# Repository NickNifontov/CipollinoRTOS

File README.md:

CipollinoRTOS 

Sin wave invertor (HRPWM, 35kHz). Replacement for TL/EG PWM .

@Copyright (c) Nick Nifontov. All rights reserved.

E-mail: 3318798@gmail.com

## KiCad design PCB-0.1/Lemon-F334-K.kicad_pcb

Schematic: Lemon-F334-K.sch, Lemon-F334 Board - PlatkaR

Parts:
BZ1: Buzzer; Buzzer_TDK_PS1240P02BT_D12.2mm_H6.5mm
BZ2: Buzzer; MagneticBuzzer_Kingstate_KCG0601
BZ3: Buzzer; Buzzer_12x9.5RM7.6
C1, C3, C5, C7, C8, C14, C15, C23, C24, C27, C31, C36, C37, C38, C39, C40: 100nf; C_0805_2012Metric; LCSC Part #（optional） C49678
C2, C4, C6, C16, C17, C18, C19, C25, C26, C28, C29, C43, C44, C45, C47, C51: 10uf; C_0805_2012Metric; LCSC Part #（optional） C15850
C9, C10: 12pf; C_0805_2012Metric; LCSC Part #（optional） C1792
C11, C12, C13, C20, C21, C22, C46, C48, C49, C50: 10uf; C_1206_3216Metric; LCSC Part #（optional） C13585
C30: 220nf; C_0805_2012Metric; LCSC Part #（optional） C5378
C32, C34: 100pf; C_0805_2012Metric; LCSC Part #（optional） C1790
C33, C35: 1nf; C_0805_2012Metric; LCSC Part #（optional） C46653
C41, C42: 100uf; CP_EIA-3528-21_Kemet-B
D1: S210; D_SMA; LCSC Part #（optional） C14996
D2, D3, D4, D5, D6, D8, D9, D11, D12, D13, D14, D15, D24, D25: D_Zener_Small_ALT; D_MiniMELF; LCSC Part #（optional） C8056
D7, D10, D26, D27: BAS; D_SOD-123; LCSC Part #（optional） C8598
D16, D18, D20, D22: LED; LED_0805_2012Metric; LCSC Part #（optional） C2296
D17, D19, D21, D23: LED; LED_D3.0mm
D28: P6KE18A(CA); D_DO-15_P15.24mm_Horizontal
D29: P6KE18A(CA); D_DO-15_P10.16mm_Horizontal
D30: 1.5KE20-30A(CA); D_DO-201_P12.70mm_Horizontal
H1, H2: MountingHole_Pad; MountingHole_2.2mm_M2_DIN965_Pad
J1: Conn_01x21_Male; PinHeader_1x21_P2.54mm_Horizontal
J2: Conn_01x21_Male; PinHeader_1x02_P2.54mm_Vertical
J3: UCC27424DR; SOP-8_3.9x4.9mm_P1.27mm; LCSC Part #（optional） C138519
J4: Conn_01x21_Male; PinHeader_1x04_P2.54mm_Vertical
L1: bead; L_0805_2012Metric; LCSC Part #（optional） C1017
Q1, Q2, Q6, Q8, Q9: BC817; SOT-23; LCSC Part #（optional） C2145
Q3, Q4, Q5, Q7: BCX56; SOT-89-3; LCSC Part #（optional） C9634
R1, R14, R30, R61: 4K7; R_0805_2012Metric; LCSC Part #（optional） C17673
R2, R3, R4, R7, R11, R20, R23, R26, R28, R29, R31, R32, R37, R38, R42, R43, R57, R62, R63, R65: 10K; R_0805_2012Metric; LCSC Part #（optional） C17414
R5: 100K; R_0805_2012Metric; LCSC Part #（optional） C17407
R6, R46, R51: 20K; R_0805_2012Metric; LCSC Part #（optional） C4328
R8: 5K6; R_0805_2012Metric; LCSC Part #（optional） C4382
R9, R50: 3K3; R_0805_2012Metric; LCSC Part #（optional） C26010
R10: 100; R_1206_3216Metric; LCSC Part #（optional） C17901
R12, R17, R18, R19, R22, R25, R33, R34, R36, R40, R41, R47, R52, R53, R54, R55, R56, R64: 1K; R_0805_2012Metric; LCSC Part #（optional） C17513
R13: 0; R_0805_2012Metric; LCSC Part #（optional） C17477
R15, R16: 2; R_0805_2012Metric; LCSC Part #（optional） C17606
R21, R24, R27, R45, R58, R66: 2K2; R_0805_2012Metric; LCSC Part #（optional） C17520
R35, R39, R48, R59, R60: 100; R_0805_2012Metric; LCSC Part #（optional） C17408
R44, R49: 15K; R_0805_2012Metric; LCSC Part #（optional） C17475
RV1, RV2, RV3, RV4: R_POT; Potentiometer_Bourns_3296X_Horizontal
U2, U3: LM317_3PinPackage; TO-252-2
U4: STM32F334C8Tx; LQFP-48_7x7mm_P0.5mm; LCSC Part #（optional） C99450
Y1: Crystal_GND24; Crystal_SMD_3225-4Pin_3.2x2.5mm; LCSC Part #（optional） C9002

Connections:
16V: D1.2 (A), J1.7
50HZ_1: J1.15, Q3.2 (C), R21.1
50HZ_2: J1.17, Q4.2 (C), R24.1
50HZ_A: D4.1 (K), R19.2, U4.19 (PB1)
50HZ_B: D5.1 (K), R22.2, U4.26 (PB13)
+3V3: C2.2, C3.2, C4.2, C5.2, C19.2, C24.2, C25.2, C26.2, C27.1, C28.1, C39.1, C41.1, C42.1, C51.2, J4.1, L1.2, R3.1, R4.1, R9.1, R20.2, R23.2, R26.2, R28.2, R32.1, R63.1, RV3.1, RV4.1, U3.2 (VO), U4.1 (VBAT), U4.24 (VDD), U4.36 (VDD), U4.48 (VDD)
+12V: C15.2, C16.2, C17.2, C18.2, C29.2, C30.2, C43.1, C44.1, C45.1, C47.2, J3.6, R7.1, R10.1, R21.2, R24.2, R27.2, R44.2, R48.1, R58.2, R66.2, U2.2 (VO)
+15V: C11.2, C12.2, C13.2, C14.2, C20.2, C21.2, C22.2, C23.2, C46.2, C48.2, C49.2, C50.2, D1.1 (K), D30.1 (K), U2.3 (VI), U3.3 (VI)
AB: J1.6, R46.2
ADC-15V: C36.2, D13.1 (K), R44.1, R45.2, U4.15 (PA5), U4.22 (PB11)
ADC-AB: C37.2, D14.1 (K), R46.1, R47.2, U4.27 (PB14)
ADC-OC-I: C33.1, D9.1 (K), R37.1, R38.2, U4.10 (PA0)
ADC-OC-V: C35.1, D11.1 (K), R42.1, R43.2, U4.11 (PA1)
ADC_TEMP: C38.1, D15.1 (K), R49.2, R50.1, U4.28 (PB15)
BLOCK-PEREK: J1.1, R30.2
BUZZER: R12.1, U4.46 (PB9)
BUZZER_LEVEL: RV3.2, U4.20 (PB2)
CLK: J4.3, R29.2, U4.37 (PA14)
CMD-BLOCK-PEREK: C31.2, Q6.3 (C), R32.2, U4.45 (PB8)
CMD-START-STOP: C8.2, Q1.3 (C), R3.2, U4.2 (PC13), U4.38 (PA15), U4.43 (PB7)
COOLER1: J1.8, Q7.2 (C), R58.1
COOLER1_CMD: R56.1, U4.30 (PA9)
CURRENT-PROTECTION-POLKA: D7.2 (A), J1.3
DIO: J4.2, R28.1, U4.34 (PA13)
DRV_SD: J3.1, J3.8, R14.2, U4.42 (PB6)
GND: C1.1, C2.1, C3.1, C4.1, C5.1, C6.2, C7.2, C8.1, C9.1, C10.1, C11.1, C12.1, C13.1, C14.1, C15.1, C16.1, C17.1, C18.1, C19.1, C20.1, C21.1, C22.1, C23.1, C24.1, C25.1, C26.1, C27.2, C28.2, C29.1, C30.1, C31.1, C32.1, C33.2, C34.1, C35.2, C36.1, C37.1, C38.2, C39.2, C40.1, C41.2, C42.2, C43.2, C44.2, C45.2, C46.1, C47.1, C48.1, C49.1, C50.1, C51.1, D2.2 (A), D3.2 (A), D4.2 (A), D5.2 (A), D6.2 (A), D8.2 (A), D9.2 (A), D11.2 (A), D12.2 (A), D13.2 (A), D14.2 (A), D15.2 (A), D24.2 (A), D25.2 (A), D28.2 (A), D29.2 (A), D30.2 (A), J1.5, J3.3, J4.4, Q1.2 (E), Q2.2 (E), Q3.3 (E), Q4.3 (E), Q5.3 (E), Q6.2 (E), Q7.3 (E), Q8.2 (E), Q9.2 (E), R2.2, R5.2, R6.2, R8.2, R11.2, R14.1, R29.1, R31.2, R35.1, R36.1, R38.1, R39.1, R41.1, R43.1, R45.1, R47.1, R50.2, R51.2, R52.1, R53.1, R54.1, R55.1, R57.2, R62.2, R65.2, RV3.3, RV4.3, U4.8 (VSSA), U4.23 (VSS), U4.35 (VSS), U4.47 (VSS), Y1.2, Y1.4
IGLA: J1.13, Q5.2 (C), R27.1
IGLA_CMD: D6.1 (K), R25.2, U4.41 (PB5)
LED_AB: D18.2 (A), D19.2 (A), U4.40 (PB4)
LED_I: D20.2 (A), D21.2 (A), J1.16, U4.3 (PC14)
LED_TEMP: D16.2 (A), D17.2 (A), U4.21 (PB10)
LED_V: D22.2 (A), D23.2 (A), J1.14, U4.4 (PC15)
unnamed: BZ1.1 (-), BZ2.1 (-), BZ3.1 (-), R10.2
unnamed: BZ1.2 (+), BZ2.2 (+), BZ3.2 (+), J2.2, R13.2
unnamed: C1.2, R4.2, U4.7 (NRST)
unnamed: C6.1, C7.1, L1.1, U4.9 (VDDA)
unnamed: D7.1 (K), R33.2
unnamed: D10.1 (K), RV2.1
unnamed: D16.1 (K), D17.1 (K), R52.2
unnamed: D18.1 (K), D19.1 (K), R53.2
unnamed: D20.1 (K), D21.1 (K), R54.2
unnamed: D22.1 (K), D23.1 (K), R55.2
unnamed: D26.1 (K), R42.2
unnamed: D26.2 (A), R40.2, RV2.2
unnamed: D27.1 (K), R37.2
unnamed: D27.2 (A), R34.2, RV1.2
unnamed: H1.1, U4.14 (PA4)
unnamed: H2.1, U4.16 (PA6)
unnamed: J2.1, Q2.3 (C), R13.1
unnamed: J3.2, R18.1
unnamed: J3.4, R17.1
unnamed: Q1.1 (B), R1.1, R2.1
unnamed: Q2.1 (B), R11.1, R12.2
unnamed: Q3.1 (B), R19.1, R20.1
unnamed: Q4.1 (B), R22.1, R23.1
unnamed: Q5.1 (B), R25.1, R26.1
unnamed: Q6.1 (B), R30.1, R31.1
unnamed: Q7.1 (B), R56.2, R57.1
unnamed: Q8.1 (B), R61.1, R62.1
unnamed: Q9.1 (B), R64.2, R65.1
unnamed: R5.1, U4.44 (BOOT0)
unnamed: R6.1, R7.2, U2.1 (ADJ)
unnamed: R8.1, R9.2, U3.1 (ADJ)
unnamed: R33.1, RV1.1
unnamed: R35.2, RV1.3
unnamed: R39.2, RV2.3
OC: D10.2 (A), J1.19
OC-I: C32.2, D8.1 (K), R34.1, R36.2, U4.18 (PB0)
OC-V: C34.2, D12.1 (K), R40.1, R41.2, U4.17 (PA7)
PF0_: C9.2, U4.5 (PF0), Y1.1
PF1_: C10.2, U4.6 (PF1), Y1.3
PWM1: J1.9, R16.1
PWM1_X: D29.1 (K), J3.7, R16.2
PWM2: J1.11, R15.2
PWM2_X: D28.1 (K), J3.5, R15.1
PWM_IN1: D3.1 (K), R18.2, U4.29 (PA8)
PWM_IN2: D2.1 (K), R17.2, U4.31 (PA10)
RX_IN: D25.1 (K), R60.2, U4.13 (PA3)
RX_OUT: J1.4, R60.1
START-STOP: J1.21, R1.2
SYNC-A: C40.2, Q8.3 (C), R63.2, U4.33 (PA12), U4.39 (PB3)
SYNC-A-IN: J1.10, R61.2
SYNC-CMD: R64.1, U4.32 (PA11)
SYNC-CMD-OUT: J1.12, Q9.3 (C), R66.1
TEMP_A: J1.20, R48.2
TEMP_B: J1.18, R49.1, R51.1
TEMP_LEVEL: RV4.2, U4.25 (PB12)
TX_IN: D24.1 (K), R59.2, U4.12 (PA2)
TX_OUT: J1.2, R59.1

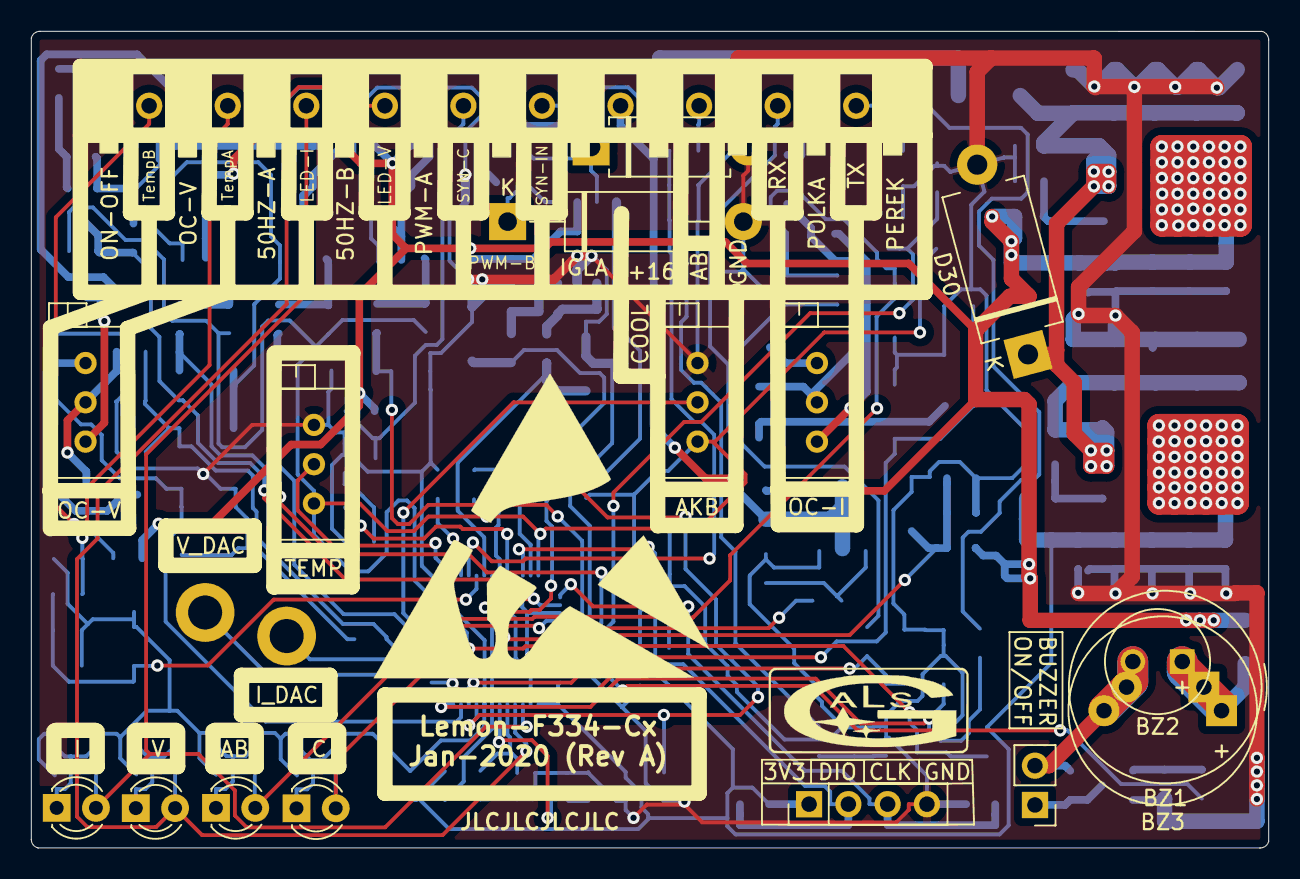
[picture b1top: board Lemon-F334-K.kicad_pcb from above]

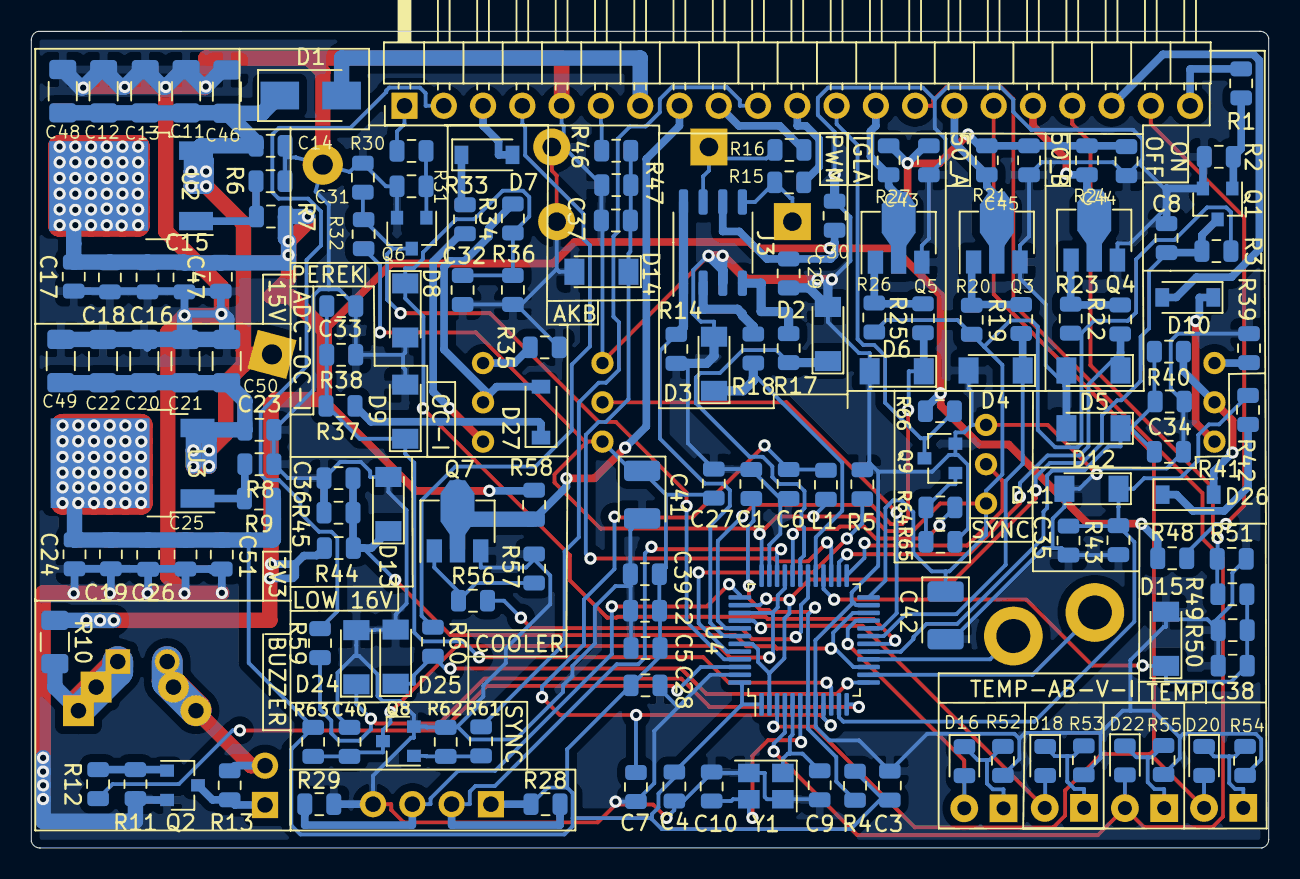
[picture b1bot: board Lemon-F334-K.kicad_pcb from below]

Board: 2 copper layers, 80.0 x 52.8 mm, 174 parts (156 on the bottom side), 89 nets.

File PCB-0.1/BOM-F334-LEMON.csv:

Comment,Designator,Footprint,LCSC Part #(optional)
100nf,"C31,C1,C3,C5,C7,C8,C14,C15,C23,C24,C36,C37,C38,C27,C39,C40",0805_C,C49678
BC817,"Q1,Q2,Q6,Q8,Q9",SOT-23,C2145
4K7,"R1,R14,R30,R61",0805_R,C17673
10K,"R2,R3,R4,R7,R11,R20,R23,R26,R28,R29,R31,R32,R37,R38,R42,R43,R57,R62,R63,R65",0805_R,C17414
S210,D1,D_SMA,C14996
bead,L1,L_0805_2012Metric,C1017
100K,R5,0805_R,C17407
10uf,"C2,C4,C6,C16,C17,C18,C19,C25,C26,C28,C29,C43,C44,C45,C47,C51",0805_C,C15850
12pf,"C9,C10",0805_C,C1792
Crystal_GND24,Y1,Crystal_SMD_3225-4Pin_3.2x2.5mm,C9002
20K,"R6,R46,R51",0805_R, C4328
LM317_3PinPackage,"U2,U3",TO-252-2,C75510
5K6,R8,0805_R,C4382
3K3,"R9,R50",0805_R,C26010
100,R10,R_1206_3216Metric,C17901
1K,"R12,R17,R18,R19,R22,R25,R33,R34,R36,R40,R41,R47,R52,R53,R54,R55,R56,R64",0805_R,C17513
0,R13,0805_R,C17477
220nf,C30,0805_C,C5378
UCC27424DR,J3,SOP-8_3.9x4.9mm_P1.27mm,C138519
2,"R15,R16",0805_R,C17606
D_Zener_Small_ALT,"D2,D3,D4,D5,D6,D8,D9,D11,D12,D13,D14,D15,D24,D25",D_MiniMELF,C8056
BCX56,"Q3,Q4,Q5,Q7",SOT-89-3,C9634
2K2,"R21,R24,R27,R45,R58,R66",0805_R,C17520
100pf,"C32,C34",0805_C,C1790
BAS,"D7,D10,D26,D27",D_SOD-123,C8598
100,"R35,R39,R48,R59,R60",0805_R,C17408
1nf,"C33,C35",0805_C,C46653
15K,"R44,R49",0805_R,C17475
LED,"D16,D18,D20,D22",LED_0805_2012Metric,C2296
STM32F334C8Tx,U4,LQFP-48_7x7mm_P0.5mm,C99450
100uf,"C41,C42",CP_EIA-3528-21_Kemet-B,C16133
10uf,"C11,C12,C13,C46,C48,C20,C21,C22,C49,C50",C_1206_3216Metric,C13585

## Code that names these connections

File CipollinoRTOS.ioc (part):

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Mcu.Name=STM32F334C(4-6-8)Tx
Mcu.Package=LQFP48
Mcu.UserName=STM32F334C8Tx
PA0.GPIOParameters=GPIO_Label
PA0.GPIO_Label=ADC-OC-I
PA0.Mode=IN1-Single-Ended
PA0.Signal=ADC1_IN1
PA1.GPIOParameters=GPIO_Label
PA1.GPIO_Label=ADC-OC-V
PA1.Mode=IN2-Single-Ended
PA1.Signal=ADC1_IN2
PA10.GPIOParameters=GPIO_Label
PA10.GPIO_Label=PWM2
PA10.Mode=Output_TB1
PA10.Signal=HRTIM1_CHB1
PA11.GPIOParameters=GPIO_Speed,GPIO_Label
PA11.GPIO_Label=SYNC-CMD
PA11.GPIO_Speed=GPIO_SPEED_FREQ_HIGH
PA11.Signal=GPIO_Output
PA12.GPIOParameters=GPIO_Label,GPIO_ModeDefaultEXTI
PA12.GPIO_Label=SYNC-A
PA12.GPIO_ModeDefaultEXTI=GPIO_MODE_IT_RISING_FALLING
PA12.Signal=GPXTI12
PA13.GPIOParameters=GPIO_Label
PA13.GPIO_Label=DIO
PA13.Mode=Serial_Wire
PA13.Signal=SYS_JTMS-SWDIO
PA14.GPIOParameters=GPIO_Label
PA14.GPIO_Label=CLK
PA14.Mode=Serial_Wire
PA14.Signal=SYS_JTCK-SWCLK
PA15.GPIOParameters=GPIO_Label
PA15.GPIO_Label=PWM_FAULT
PA15.Mode=Fault_Enable2
PA15.Signal=HRTIM1_FLT2
PA2.GPIOParameters=GPIO_Label
PA2.GPIO_Label=TX
PA2.Mode=Asynchronous
PA2.Signal=USART2_TX
PA3.GPIOParameters=GPIO_Label
PA3.GPIO_Label=RX
PA3.Mode=Asynchronous
PA3.Signal=USART2_RX
PA4.GPIOParameters=GPIO_Label
PA4.GPIO_Label=DAC_V
PA4.Signal=COMP_DAC11_group
PA5.GPIOParameters=GPIO_Label
PA5.GPIO_Label=ADC-15V
PA5.Mode=IN2-Single-Ended
PA5.Signal=ADC2_IN2
PA6.GPIOParameters=GPIO_Label
PA6.GPIO_Label=DAC_I
PA6.Signal=COMP_DAC21_group
PA7.GPIOParameters=GPIO_Label
PA7.GPIO_Label=OC-V
PA7.Mode=INP
PA7.Signal=COMP2_INP
PA8.GPIOParameters=GPIO_Label
PA8.GPIO_Label=PWM1
PA8.Mode=Output_TA1
PA8.Signal=HRTIM1_CHA1
PA9.GPIOParameters=GPIO_Speed,GPIO_Label
PA9.GPIO_Label=COOLER_PWM
PA9.GPIO_Speed=GPIO_SPEED_FREQ_HIGH
PA9.Signal=S_TIM2_CH3
PB0.GPIOParameters=GPIO_Label
PB0.GPIO_Label=OC-I
PB0.Mode=INP
PB0.Signal=COMP4_INP
PB1.GPIOParameters=GPIO_Speed,GPIO_Label
PB1.GPIO_Label=PWM50HZ_A
PB1.GPIO_Speed=GPIO_SPEED_FREQ_HIGH
PB1.Signal=GPIO_Output
PB10.GPIOParameters=GPIO_Speed,GPIO_Label
PB10.GPIO_Label=LED_TEMP
PB10.GPIO_Speed=GPIO_SPEED_FREQ_HIGH
PB10.Signal=GPIO_Output
PB12.GPIOParameters=GPIO_Label
PB12.GPIO_Label=TEMP_LEVEL
PB12.Mode=IN13-Single-Ended
PB12.Signal=ADC2_IN13
PB13.GPIOParameters=GPIO_Speed,GPIO_Label
PB13.GPIO_Label=PWM50HZ_B
PB13.GPIO_Speed=GPIO_SPEED_FREQ_HIGH
PB13.Signal=GPIO_Output
PB14.GPIOParameters=GPIO_Label
PB14.GPIO_Label=ADC-AB
PB14.Mode=IN14-Single-Ended
PB14.Signal=ADC2_IN14
PB15.GPIOParameters=GPIO_Label
PB15.GPIO_Label=ADC_TEMP
PB15.Mode=IN15-Single-Ended
PB15.Signal=ADC2_IN15
PB2.GPIOParameters=GPIO_Label
PB2.GPIO_Label=BUZZER_LEVEL
PB2.Mode=IN12-Single-Ended
PB2.Signal=ADC2_IN12
PB3.GPIOParameters=GPIO_Label,GPIO_ModeDefaultEXTI
PB3.GPIO_Label=SYNC-A
PB3.GPIO_ModeDefaultEXTI=GPIO_MODE_IT_RISING_FALLING
PB3.Signal=GPXTI3
PB4.GPIOParameters=GPIO_Speed,GPIO_Label
PB4.GPIO_Label=LED_AB
PB4.GPIO_Speed=GPIO_SPEED_FREQ_HIGH
PB4.Signal=GPIO_Output
PB5.GPIOParameters=GPIO_Speed,GPIO_Label
PB5.GPIO_Label=IGLA_CMD
PB5.GPIO_Speed=GPIO_SPEED_FREQ_HIGH
PB5.Signal=GPIO_Output
PB6.GPIOParameters=GPIO_FM6,GPIO_Speed,GPIO_Label
PB6.GPIO_FM6=SYSCFG_CFGR1_I2C_PB6_FMP
PB6.GPIO_Label=DRV_SD
PB6.GPIO_Speed=GPIO_SPEED_FREQ_HIGH
PB6.Signal=GPIO_Output
PB7.GPIOParameters=GPIO_Label,GPIO_ModeDefaultEXTI
PB7.GPIO_Label=CMD-START-STOP
PB7.GPIO_ModeDefaultEXTI=GPIO_MODE_IT_RISING_FALLING
PB7.Signal=GPXTI7
PB8.GPIOParameters=GPIO_Label,GPIO_ModeDefaultEXTI
PB8.GPIO_Label=CMD-BLOCK-PEREK
PB8.GPIO_ModeDefaultEXTI=GPIO_MODE_IT_RISING_FALLING
PB8.Signal=GPXTI8
PB9.GPIOParameters=GPIO_Speed,GPIO_Label,GPIO_FM9
PB9.GPIO_FM9=SYSCFG_CFGR1_I2C_PB9_FMP
PB9.GPIO_Label=BUZZER
PB9.GPIO_Speed=GPIO_SPEED_FREQ_HIGH
PB9.Signal=GPIO_Output
PC13.GPIOParameters=GPIO_Label,GPIO_ModeDefaultEXTI
PC13.GPIO_Label=CMD-START-STOP
PC13.GPIO_ModeDefaultEXTI=GPIO_MODE_IT_RISING_FALLING
PC13.Signal=GPXTI13
PC14\ /\ OSC32_IN.GPIOParameters=GPIO_Speed,GPIO_Label
PC14\ /\ OSC32_IN.GPIO_Label=LED_I
PC14\ /\ OSC32_IN.GPIO_Speed=GPIO_SPEED_FREQ_HIGH
PC14\ /\ OSC32_IN.Signal=GPIO_Output
PC15\ /\ OSC32_OUT.GPIOParameters=GPIO_Speed,GPIO_Label
PC15\ /\ OSC32_OUT.GPIO_Label=LED_V
PC15\ /\ OSC32_OUT.GPIO_Speed=GPIO_SPEED_FREQ_HIGH
PC15\ /\ OSC32_OUT.Signal=GPIO_Output
PF0\ /\ OSC_IN.GPIOParameters=GPIO_Label
PF0\ /\ OSC_IN.GPIO_Label=OSC_IN
PF0\ /\ OSC_IN.Mode=HSE-External-Oscillator
PF0\ /\ OSC_IN.Signal=RCC_OSC_IN
PF1\ /\ OSC_OUT.GPIOParameters=GPIO_Label
PF1\ /\ OSC_OUT.GPIO_Label=OSC_OUT
PF1\ /\ OSC_OUT.Mode=HSE-External-Oscillator
PF1\ /\ OSC_OUT.Signal=RCC_OSC_OUT
RCC.HSEPLLFreq_Value=12000000
RCC.HSE_VALUE=12000000
RCC.SYSCLKFreq_VALUE=72000000
RCC.SYSCLKSourceVirtual=RCC_SYSCLKSOURCE_PLLCLK
board=custom

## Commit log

2020-01-19 version 0.1. Template.
2020-01-19 added PCB (0.1 hardware platfrom)
2020-01-19 update information about project
2020-01-19 added KNOCK snippet
2020-01-19 updated Buzzer snippet
2020-01-19 fixed bug in Buzzer snippet
2020-01-19 fixed bug in Buzzer snipped (rollback function)
2020-01-19 small update description
2020-01-19 fixed bug in HRTIM and added EVENT AWD filtering
2020-01-19 small fix
2020-01-20 updated QuarkTS
2020-01-20 added CCMRAM code
2020-01-20 heap to CCMRAM
2020-01-21 Added CCMRAM and CCMRAM Data snippet code
2020-01-21 small bug fixs
2020-01-21 SysTick Interruot bug fix
